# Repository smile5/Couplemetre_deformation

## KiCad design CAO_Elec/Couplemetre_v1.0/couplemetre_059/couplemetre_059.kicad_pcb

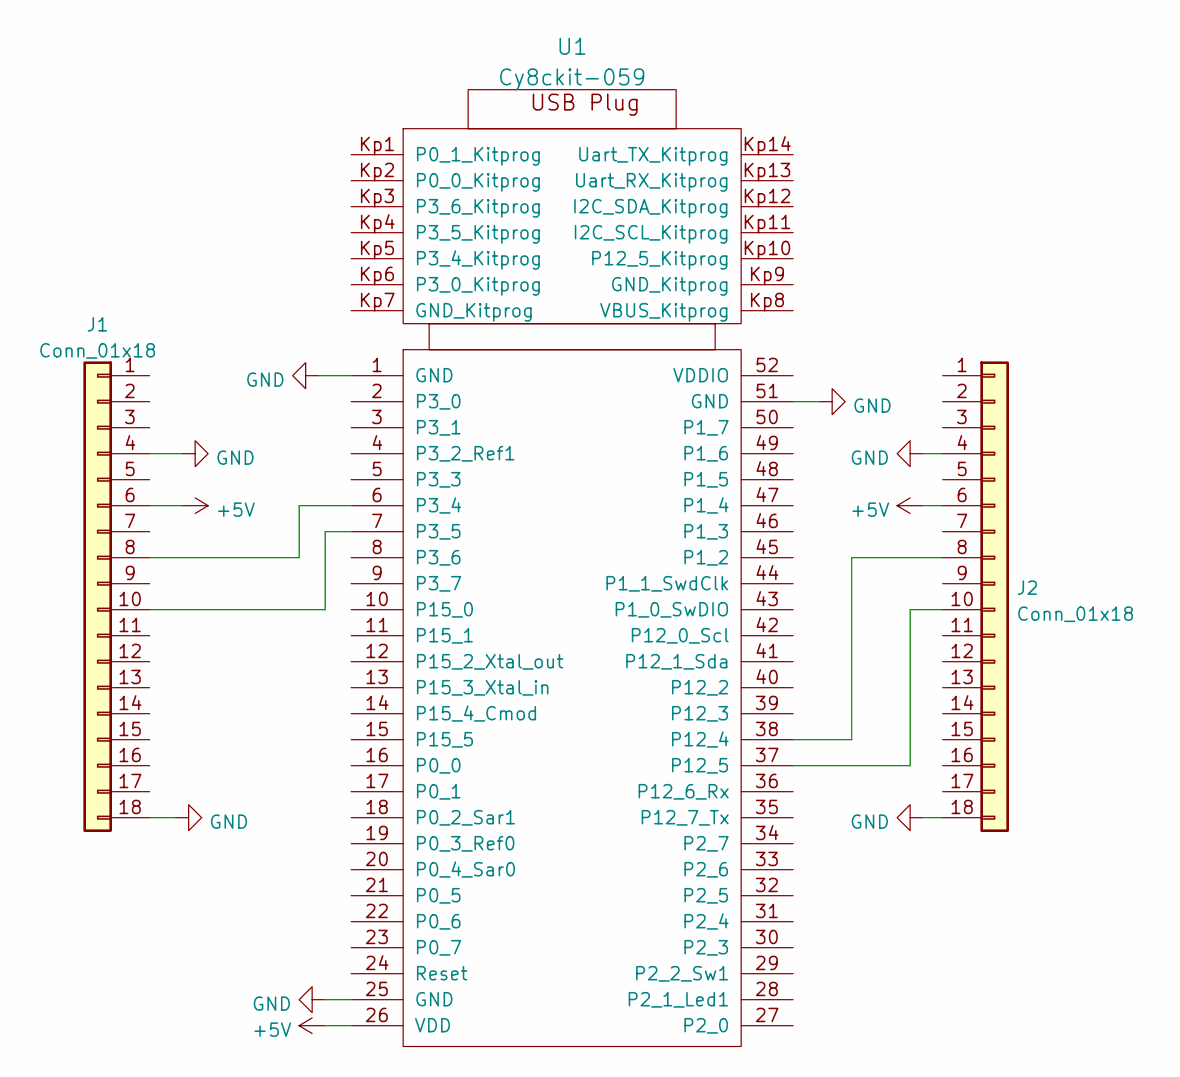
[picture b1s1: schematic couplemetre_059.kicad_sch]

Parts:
J1, J2: Conn_01x18; PinHeader_1x18_P2.54mm_Vertical
U1: Cy8ckit-059

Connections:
+5V: J1.6, J2.6, U1.26 (VDD)
GND: J1.4, J1.18, J2.4, J2.18, U1.1 (GND), U1.25 (GND), U1.51 (GND)
unnamed: J1.8, U1.6 (P3_4)
unnamed: J1.10, U1.7 (P3_5)
unnamed: J2.8, U1.38 (P12_4)
unnamed: J2.10, U1.37 (P12_5)

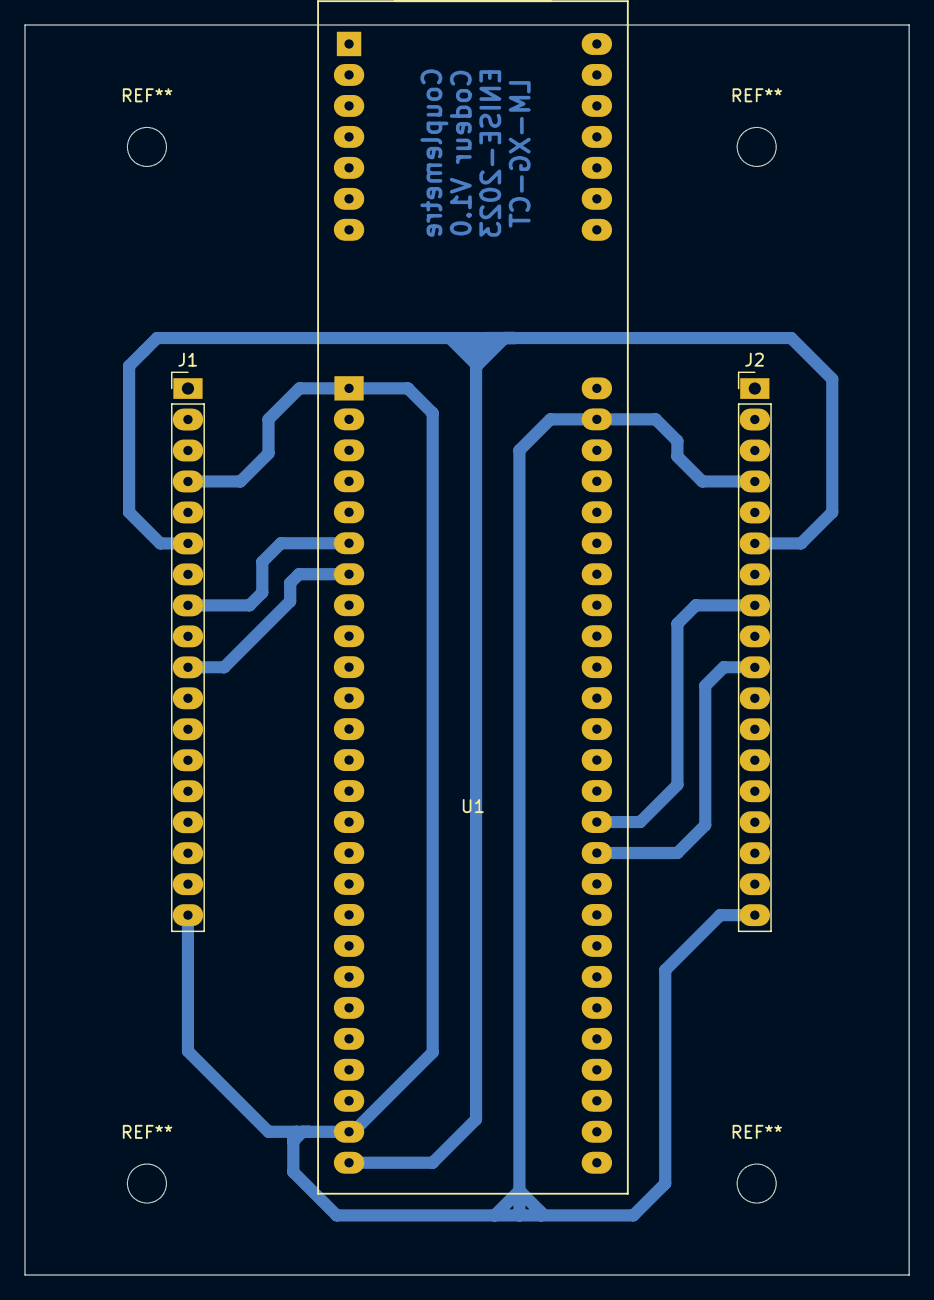
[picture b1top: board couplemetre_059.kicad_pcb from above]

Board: 2 copper layers, 72.5 x 102.5 mm, 3 parts (0 on the bottom side), 6 nets.
